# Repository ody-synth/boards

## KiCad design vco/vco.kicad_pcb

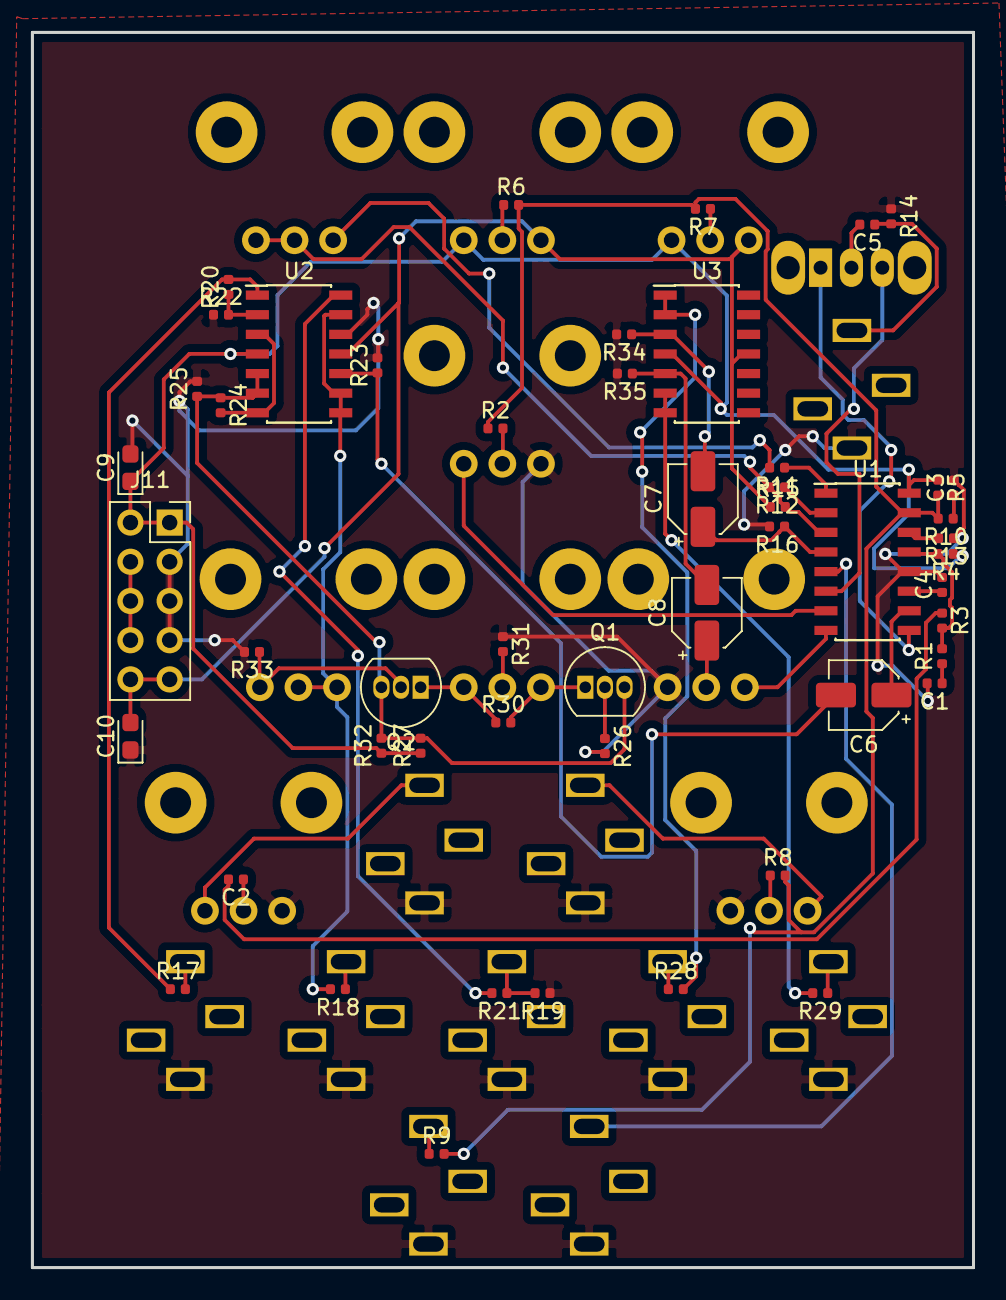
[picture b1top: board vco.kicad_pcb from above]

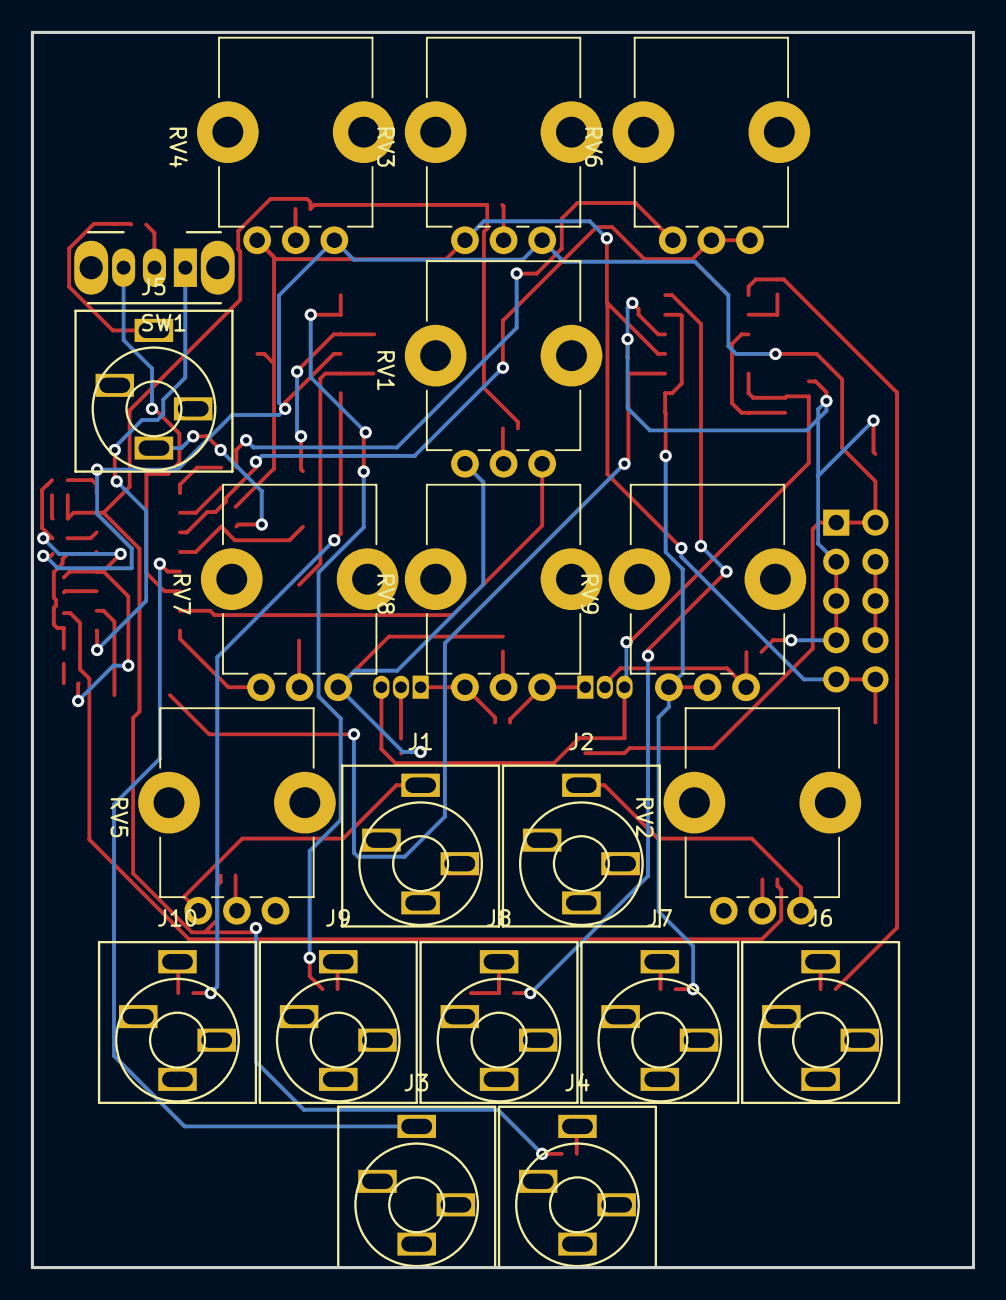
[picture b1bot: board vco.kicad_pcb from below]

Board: 2 copper layers, 61.0 x 80.0 mm, 71 parts (20 on the bottom side), 54 nets.

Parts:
C1, C3: 10nF; C_0402_1005Metric
C2: 100nF; C_0402_1005Metric
C4, C5: 1nF; C_0402_1005Metric
C6, C7, C8: 47uF; CP_Elec_4x5.4
C9, C10: 10uF; CP_EIA-2012-12_Kemet-R
J1: EXP_FM; jack_audio
J2: LIN_FM; jack_audio
J3: PWM_IN; jack_audio
J4: CV 1V/OCT; jack_audio
J5: SYNC_IN; jack_audio
J6: SINE; jack_audio
J7: TRI; jack_audio
J8: SQUARE; jack_audio
J9: PULSE; jack_audio
J10: SAW; jack_audio
J11: Conn_02x05_Odd_Even; PinSocket_2x05_P2.54mm_Vertical
Q1, Q2: 2N3904; TO-92_Inline
R1, R10, R26, R33: 470; R_0402_1005Metric
R2, R3: 1M; R_0402_1005Metric
R4: 1.5M; R_0402_1005Metric
R5: 360K; R_0402_1005Metric
R6: 1.2M; R_0402_1005Metric
R7: 5.6M; R_0402_1005Metric
R8, R9, R14: 100K; R_0402_1005Metric
R11: 24K; R_0402_1005Metric
R12: 5.6K; R_0402_1005Metric
R13: 1.8k; R_0402_1005Metric
R15: 820; R_0402_1005Metric
R16: 51K; R_0402_1005Metric
R17, R18, R28, R29: 1K; R_0402_1005Metric
R19: 82K; R_0402_1005Metric
R20, R22, R23, R27, R32, R34, R35: 10K; R_0402_1005Metric
R21: 15K; R_0402_1005Metric
R24, R25: 22K; R_0402_1005Metric
R30: 220; R_0402_1005Metric
R31: 68K; R_0402_1005Metric
RV1: 20K; Potentiometer_Bourns_PTV09A-1_Single_Vertical
RV2, RV3, RV4, RV5: 100k; Potentiometer_Bourns_PTV09A-1_Single_Vertical
RV6, RV7: 10K; Potentiometer_Bourns_PTV09A-1_Single_Vertical
RV8: 50K; Potentiometer_Bourns_PTV09A-1_Single_Vertical
RV9: 100K; Potentiometer_Bourns_PTV09A-1_Single_Vertical
SW1: SW_SPDT; SW_CuK_OS102011MA1QN1_SPDT_Angled
U1: AS3340; SOIC-16_3.9x9.9mm_P1.27mm
U2, U3: TL074; SOIC-14_3.9x8.7mm_P1.27mm

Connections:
+12V: C9.1, J11.1, J11.2, R4.1, R5.1, R27.1, R32.1, RV3.1, RV4.1, U1.16, U2.4, U3.4
-12V: C10.2, J11.9, J11.10, R15.1, RV3.3, RV4.3, U2.11, U3.11
GND: C1.2, C3.2, C4.2, C9.2, C10.1, J1.S, J2.S, J3.S, J4.S, J5.S, J6.S, J7.S, J8.S, J9.S, J10.S, J11.3, J11.5, J11.7, R13.1, R14.1, R16.2, R19.1, R22.1, R23.2, R25.2, R26.2, R31.1, R33.2, R34.2, R35.2, RV1.3, RV2.3, RV5.1, RV7.1, U1.12, U2.12
unnamed: C1.1, R1.1
unnamed: C2.1, RV2.2
unnamed: C2.2, R3.1
unnamed: C3.1, R10.1
unnamed: C4.1, U1.11
unnamed: C5.1, J5.T, R14.2
unnamed: C5.2, SW1.2
unnamed: C6.2, R23.1, U2.10
unnamed: C7.2, R34.1, U3.3
unnamed: C8.2, R35.1, U3.5
unnamed: J1.T, RV5.3
unnamed: J2.T, RV2.1
unnamed: J4.T, R9.1
unnamed: J6.T, R17.2
unnamed: J7.T, R18.1
unnamed: J8.T, R19.2, R21.1
unnamed: J9.T, R28.1
unnamed: J10.T, R29.1
unnamed: J11.4, J11.6, J11.8
unnamed: Q1.1, R30.2, RV8.3
unnamed: Q1.2, R26.1
unnamed: Q1.3, Q2.3, R24.1, R25.1, R27.2, R32.2, U2.5, U2.6
unnamed: Q2.1, R30.1, RV8.1
unnamed: Q2.2, R33.1, RV9.1
unnamed: R2.2, RV1.2
unnamed: R6.1, RV3.2
unnamed: R7.1, RV4.2
unnamed: R8.1, RV5.2
unnamed: R11.1, U1.1
unnamed: R11.2, RV6.3
unnamed: R12.1, U1.2
unnamed: R13.2, U1.14
unnamed: R17.1, R20.2, U2.1
unnamed: R20.1, R22.2, U2.2
unnamed: R21.2, U2.14
unnamed: R24.2, U2.3, U2.7
unnamed: R28.2, U3.1, U3.2
unnamed: R29.2, U3.6, U3.7
unnamed: R31.2, RV8.2
unnamed: RV7.3, U1.8
PULSE: C7.1, R16.1, U1.4
REE: R12.2, R15.2, RV6.1, RV6.2, U1.3
SAW: C8.1, RV7.2
TRIANGLE: C6.1, U1.10
TRI_OUT: R18.2, RV9.2, RV9.3, U2.8, U2.9, U2.13
VFCI: R2.1, R5.2, R6.2, R7.2, R8.2, R9.2, R10.2, U1.15
VHFT: RV1.1, U1.7
VHSI: SW1.3, U1.6
VLFI: R1.2, R3.2, R4.2, U1.13
VPWM: J3.T, U1.5
VSSI: SW1.1, U1.9

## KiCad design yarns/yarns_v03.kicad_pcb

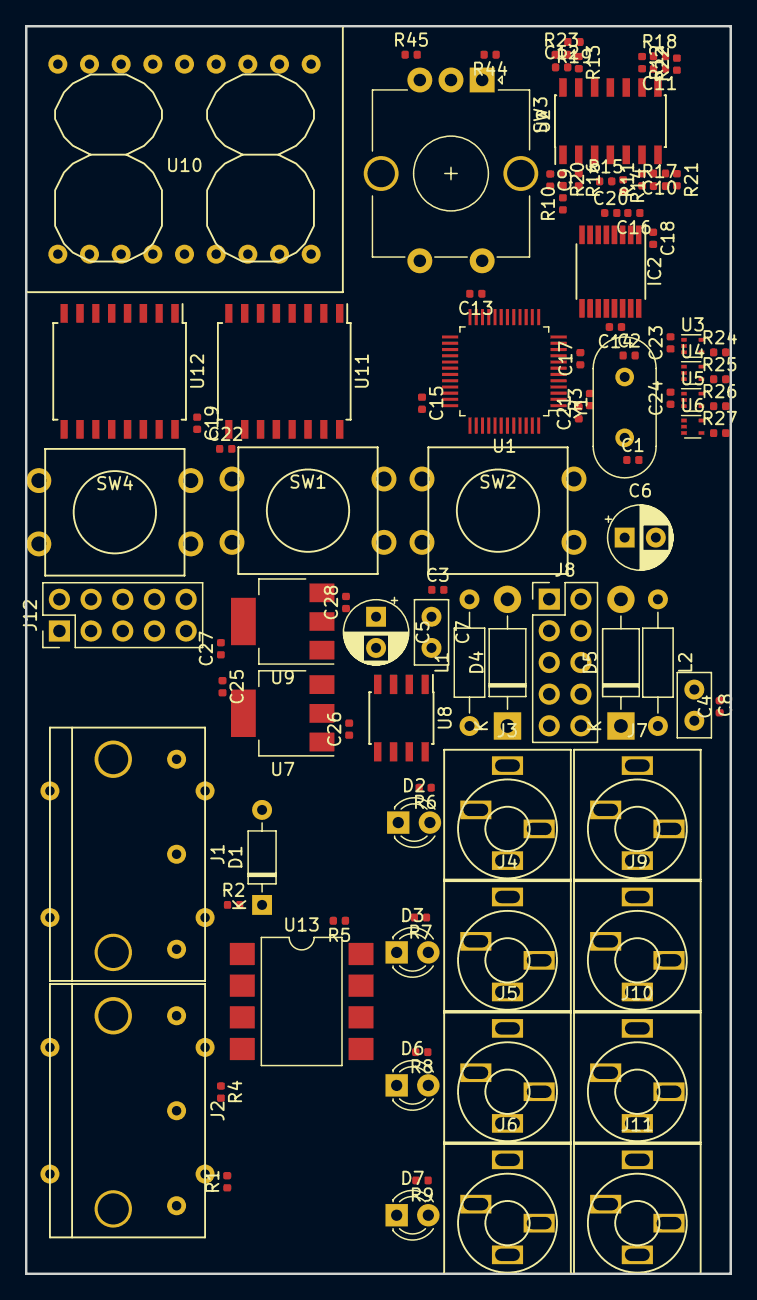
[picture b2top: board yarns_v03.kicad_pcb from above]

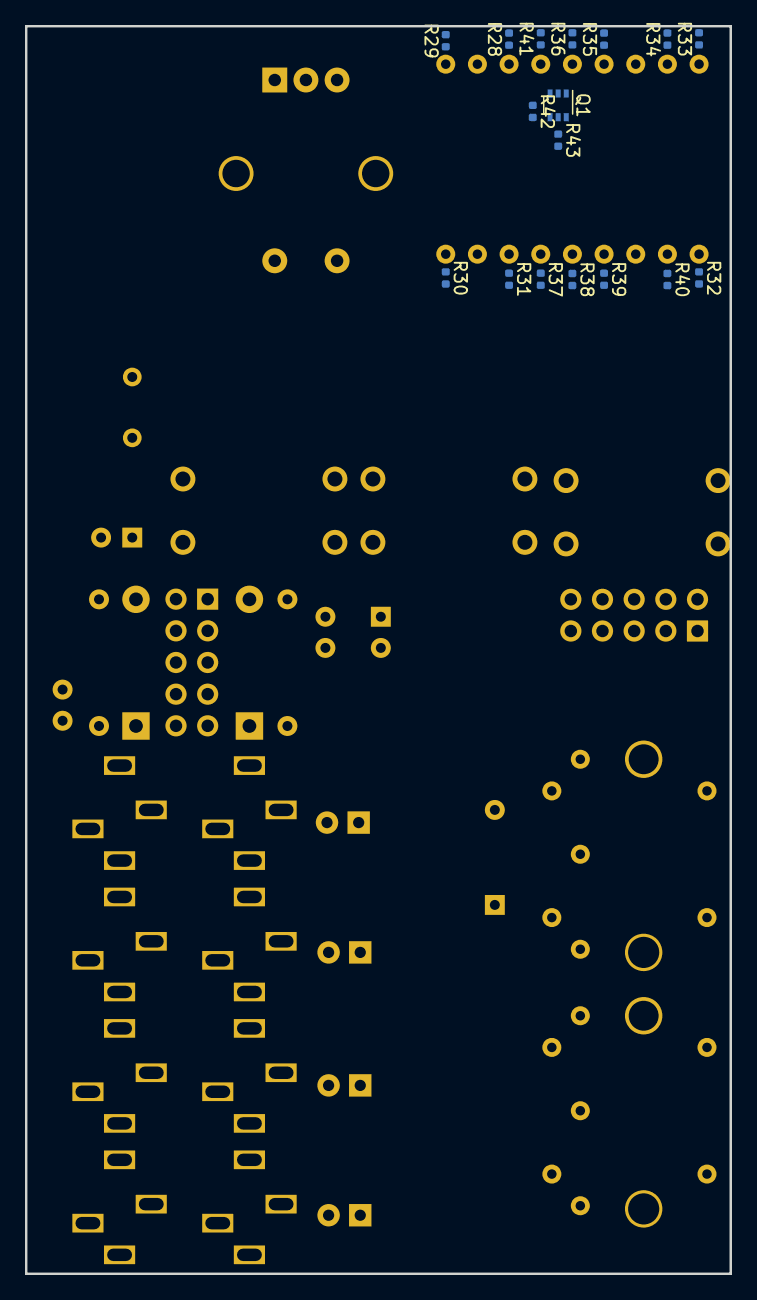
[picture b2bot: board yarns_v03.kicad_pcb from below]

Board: 2 copper layers, 56.5 x 100.1 mm, 114 parts (17 on the bottom side), 112 nets, no tracks yet.

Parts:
C1, C2, C9, C10, C11, C12: 18p; C_0402_1005Metric
C3, C4, C13, C14, C15, C17, C18, C19, C21, C22, C23, C24, C25: 100n; C_0402_1005Metric
C5, C6: 10uF; CP_Radial_D5.0mm_P2.50mm
C7, C8: 100nF; C_Disc_D5.0mm_W2.5mm_P2.50mm
C16: 220n; C_0402_1005Metric
C20: 3.3u; C_0402_1005Metric
C26: 10u; C_0402_1005Metric
C27, C28: 1u; C_0402_1005Metric
D1: 1N4148; D_DO-35_SOD27_P7.62mm_Horizontal
D2, D3, D6, D7: 3MM; LED_D3.0mm
D4, D5: 1N4007; D_DO-41_SOD81_P10.16mm_Horizontal
IC2: DAC8564; TSSOP-16_4.4x5mm_P0.65mm
J1, J2: DIN-5_180degree; MIDI_IN
J3, J4, J5, J6, J7, J9, J10, J11: AudioJack3_Ground; jack_audio
J8, J12: Conn_02x05_Odd_Even; PinHeader_2x05_P2.54mm_Vertical
L1, L2: 22uH; L_Axial_L5.3mm_D2.2mm_P10.16mm_Horizontal_Vishay_IM-1
Q1: MBT3904DW1; SOT-363_SC-70-6
R1, R4: 51; R_0402_1005Metric
R2: 220; R_0402_1005Metric
R3, R5: 10k; R_0402_1005Metric
R6, R7, R8, R9, R28, R29, R30, R31, R32, R33, R34, R35, R36, R37, R38, R39, R40, R41: 100; R_0402_1005Metric
R10, R11, R12, R13, R14, R15: 47k; R_0402_1005Metric
R16, R17, R18, R19: 240k; R_0402_1005Metric
R20, R21, R22, R23, R24, R25, R26, R27, R42, R43, R44, R45: 1k; R_0402_1005Metric
SW1, SW2, SW4: SW_Push_Dual; PUSH_BUTTON
SW3: Rotary_Encoder_Switch; RotaryEncoder_Alps_EC12E-Switch_Vertical_H20mm_CircularMoun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
U1: STM32F103CBTx; LQFP-48_7x7mm_P0.5mm
U2: OPA4134; SOIC-14_3.9x8.7mm_P1.27mm
U3, U4, U5, U6: 74AHCT1G125; SOT-553
U7: LD1117S33TR_SOT223; SOT-223-3_TabPin2
U8: REF02AU; SOIC-8_3.9x4.9mm_P1.27mm
U9: MCP1703A-5002_SOT223; SOT-223-3_TabPin2
U10: KINGBRIGHT-PDC54-11; KINGBRIGHT-PDC54-11GWA
U11, U12: 74HC595; SOIC-16W_7.5x10.3mm_P1.27mm
U13: 6N135S; SMDIP-8_W9.53mm
Y1: 8MHz; Crystal_HC49-U_Vertical

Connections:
12VC: D4.2, J8.1, J8.2
+3V3: C13.2, C14.2, C15.2, C17.2, C19.2, C21.2, C22.2, C26.2, IC2.12, J12.1, R3.1, R4.2, U1.1, U1.9, U1.24, U1.36, U1.48, U7.2, U11.10, U11.16, U12.10, U12.16
+5V: C18.2, C20.2, IC2.4, U8.6
+5VD: C23.2, C24.2, C28.2, U3.5, U4.5, U5.5, U6.5, U9.3
+12V: C3.2, C5.1, C7.1, C25.2, C27.2, L1.2, U2.4, U7.3, U8.2, U9.1
-12VC: D5.1, J8.9, J8.10
/EURORACKPIN/12Vto5V: D4.1, L1.1
CH_A: IC2.1, R10.1
CH_B: IC2.2, R11.1
CH_C: IC2.7, R12.1
CH_D: IC2.8, R13.1
DAC_MOSI: IC2.11, U1.28
DAC_SCK: IC2.10, U1.26
DAC_SS: IC2.9, U1.25
DISP_CHAR0: R42.2, U1.42
DISP_CHAR1: R43.2, U1.41
DISP_EN: U1.45, U11.12, U12.12
DISP_SCK: U1.43, U11.11, U12.11
DISP_SER: U1.46, U11.14
ENC_A: R44.1, U1.2
ENC_B: R45.1, U1.3
ENC_CLICK: SW3.S1, U1.4
GATE_A: U1.21, U3.2
GATE_B: U1.22, U4.2
GATE_C: U1.18, U5.2
GATE_D: U1.19, U6.2
GND: C1.2, C2.2, C3.1, C4.2, C5.2, C6.1, C7.2, C8.1, C13.1, C14.1, C15.1, C16.1, C17.1, C18.1, C19.1, C20.1, C21.1, C22.1, C23.1, C24.1, C25.1, C26.1, C27.1, C28.1, D2.1, D3.1, D6.1, D7.1, IC2.5, IC2.6, IC2.13, IC2.14, IC2.15, IC2.16, J2.3, J3.S, J4.S, J5.S, J6.S, J7.S, J8.3, J8.4, J8.5, J8.6, J8.7, J8.8, J9.S, J10.S, J11.S, J12.3, J12.5, J12.9, Q1.1, Q1.4, R15.1, SW1.1, SW1.3, SW2.1, SW2.3, SW3.C, SW3.S2, SW4.1, SW4.3, U1.8, U1.20, U1.23, U1.35, U1.44, U1.47, U3.1, U3.3, U4.1, U4.3, U5.1, U5.3, U6.1, U6.3, U7.1, U8.4, U9.2, U11.8, U12.8, U13.5
JTCK: J12.4, U1.37
JTDI: J12.8, U1.38
JTDO: J12.6, U1.39
JTMS: J12.2, U1.34
LED1: R6.2, U1.33
LED2: R7.2, U1.32
LED3: R8.2, U1.29
LED4: R9.2, U1.27
MIDI_RX: R5.2, U1.31, U13.6
MIDI_TX: R1.1, U1.30
unnamed: C1.1, U1.5, Y1.1
unnamed: C2.1, U1.6, Y1.2
unnamed: C9.1, R20.1, U2.1
unnamed: C9.2, R10.2, R16.1, U2.2
unnamed: C10.1, R21.1, U2.7
unnamed: C10.2, R11.2, R17.1, U2.6
unnamed: C11.1, R22.1, U2.8
unnamed: C11.2, R12.2, R18.1, U2.9
unnamed: C12.1, R23.1, U2.14
unnamed: C12.2, R13.2, R19.1, U2.13
unnamed: D1.1, R2.2, U13.2
unnamed: D1.2, J1.5, U13.3
unnamed: D2.2, R6.1
unnamed: D3.2, R7.1
unnamed: D5.2, L2.1
unnamed: D6.2, R8.1
unnamed: D7.2, R9.1
unnamed: J1.4, R2.1
unnamed: J2.4, R1.2
unnamed: J2.5, R4.1
unnamed: J3.T, R16.2, R20.2
unnamed: J4.T, R17.2, R21.2
unnamed: J5.T, R18.2, R22.2
unnamed: J6.T, R19.2, R23.2
unnamed: J7.T, R24.2
unnamed: J9.T, R25.2
unnamed: J10.T, R26.2
unnamed: J11.T, R27.2
unnamed: Q1.2, R42.1
unnamed: Q1.3, U10.11
unnamed: Q1.5, R43.1
unnamed: Q1.6, U10.16
unnamed: R5.1, U13.8
unnamed: R24.1, U3.4
unnamed: R25.1, U4.4
unnamed: R26.1, U5.4
unnamed: R27.1, U6.4
unnamed: R28.1, U10.12
unnamed: R28.2, U11.15
unnamed: R29.1, U10.10
unnamed: R29.2, U11.1
unnamed: R30.1, U10.9
unnamed: R30.2, U11.2
unnamed: R31.1, U10.7
unnamed: R31.2, U11.3
unnamed: R32.1, U10.1
unnamed: R32.2, U11.4
unnamed: R33.1, U10.18
unnamed: R33.2, U11.5
unnamed: R34.1, U10.17
unnamed: R34.2, U11.6
unnamed: R35.1, U10.15
unnamed: R35.2, U11.7
unnamed: R36.1, U10.14
unnamed: R36.2, U12.15
unnamed: R37.1, U10.6
unnamed: R37.2, U12.1
unnamed: R38.1, U10.5
unnamed: R38.2, U12.2
unnamed: R39.1, U10.4
unnamed: R39.2, U12.3
unnamed: R40.1, U10.2
unnamed: R40.2, U12.4
unnamed: R41.1, U10.13
unnamed: R41.2, U12.5
unnamed: R44.2, SW3.A
unnamed: R45.2, SW3.B
unnamed: U11.9, U12.14
RESET: J12.10, R3.2, U1.7
SWITCH_0: SW4.2, SW4.4, U1.15
SWITCH_1: SW2.2, SW2.4, U1.16
SWITCH_2: SW1.2, SW1.4, U1.14
VEE: C4.1, C6.2, C8.2, L2.2, U2.11
VREF: C16.2, IC2.3, R14.2
VREF\2: R14.1, R15.2, U2.3, U2.5, U2.10, U2.12

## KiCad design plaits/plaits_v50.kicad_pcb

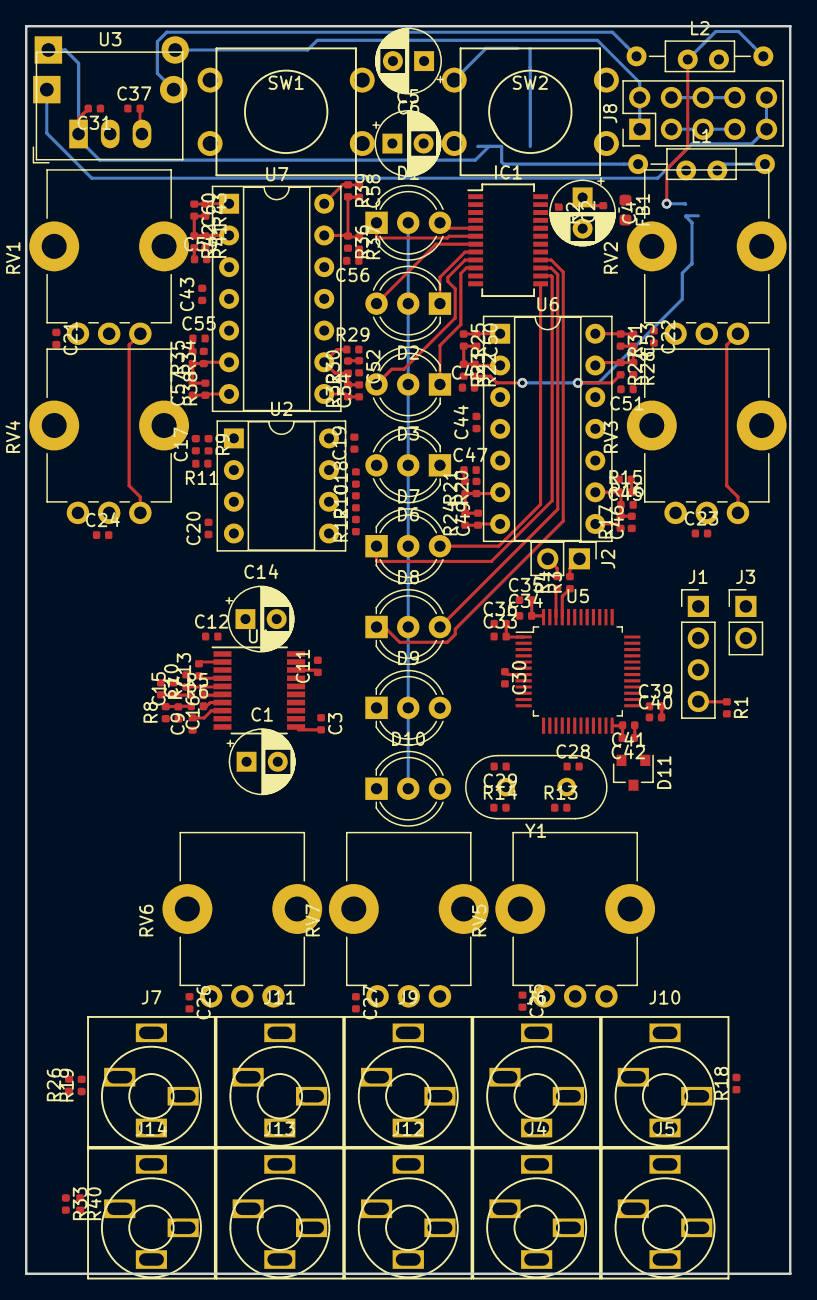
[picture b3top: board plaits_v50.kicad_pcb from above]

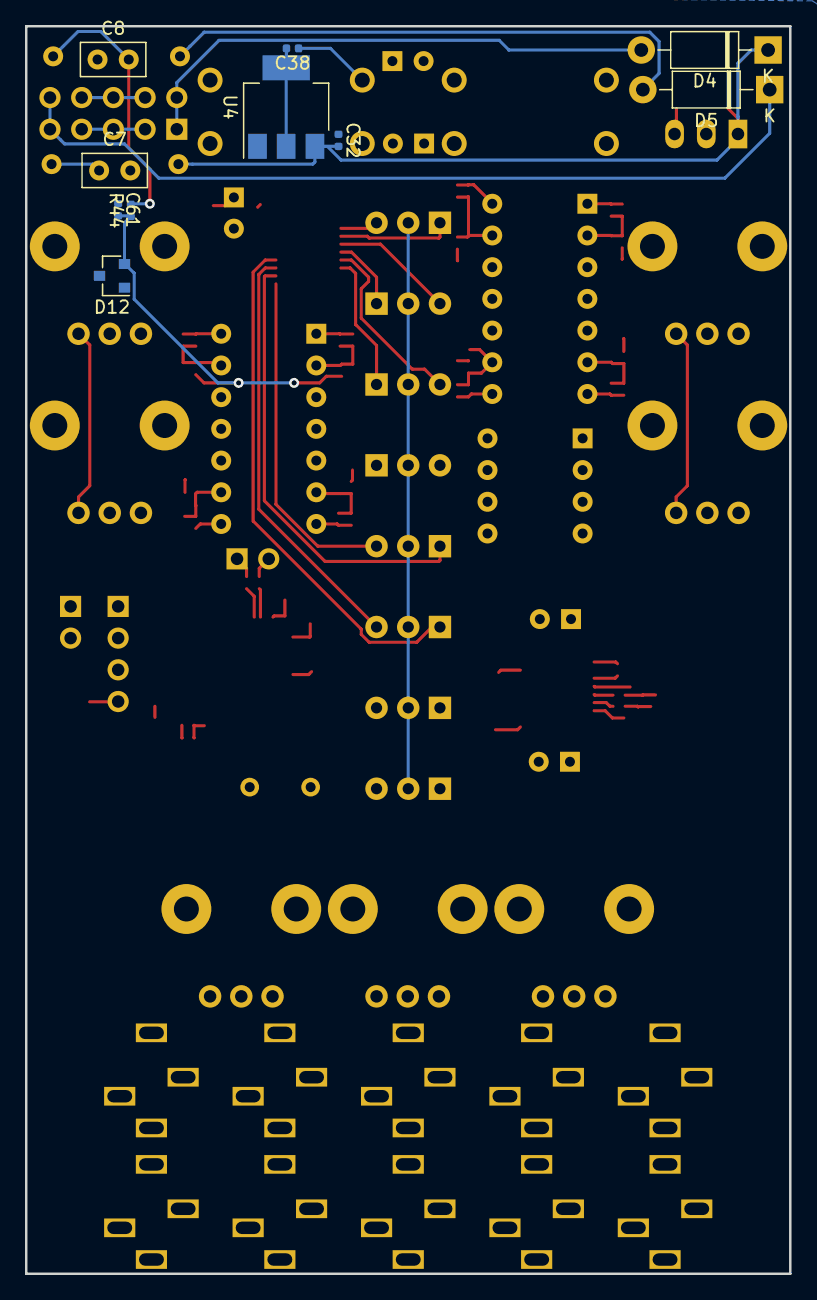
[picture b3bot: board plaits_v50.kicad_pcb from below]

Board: 2 copper layers, 61.2 x 99.9 mm, 152 parts (10 on the bottom side), 99 nets.

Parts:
C1, C4, C5, C6, C14: 10uF; CP_Radial_D5.0mm_P2.50mm
C2, C3, C9, C11, C12, C19, C20, C21, C22, C23, C24, C25, C26, C27, C30, C32, C35, C36, C40, C42, C43, C44: 100nF; C_0402_1005Metric
C7, C8: 100nF; C_Disc_D5.0mm_W2.5mm_P2.50mm
C10, C13: 2.2uF; C_0402_1005Metric
C15, C16, C46, C50, C53, C54, C57, C58: 1nF; C_0402_1005Metric
C17, C18, C49, C60: 100pF; C_0402_1005Metric
C28, C29: 20pF; C_0402_1005Metric
C31, C37, C38: 10uF; C_0402_1005Metric
C33, C34, C39, C41, C61: 1uF; C_0402_1005Metric
C45, C47, C48, C51, C52, C55, C56, C59: ESD; C_0402_1005Metric
D1, D2, D3, D6, D7, D8, D9, D10: SSL-LX3059IGW-CA; LED_D5.0mm-3
D4, D5: 1N4007; D_DO-41_SOD81_P10.16mm_Horizontal
D11: BAT54S; SOT-23
D12: LM4040DBZ-10; SOT-23
FB1: WE-CBF_0603; L_0603_1608Metric
IC1: TLC59281DBQ; SSOP-24_3.9x8.7mm_P0.635mm
J1: Conn_01x04_Male; PinHeader_1x04_P2.54mm_Vertical
J2, J3: Conn_01x02_Male; PinHeader_1x02_P2.54mm_Vertical
J4, J5, J6, J7, J9, J10, J11, J12, J13, J14: AudioJack3_Ground; jack_audio
J8: Conn_02x05_Odd_Even; PinHeader_2x05_P2.54mm_Vertical
L1, L2: 22uH; L_Axial_L5.3mm_D2.2mm_P10.16mm_Horizontal_Vishay_IM-1
R1, R2, R7, R8, R11, R18, R19, R26, R33, R40: 10k; R_0402_1005Metric
R3, R4, R13, R14: 100; R_0402_1005Metric
R5, R6, R44: 2.2k; R_0402_1005Metric
R9, R10, R24, R31, R38, R39: 33k; R_0402_1005Metric
R12: 1k; R_0402_1005Metric
R15, R21, R23, R28, R30, R35, R37, R42: 100k; R_0402_1005Metric
R16, R22, R29: 120k; R_0402_1005Metric
R17, R25, R32: 20k; R_0402_1005Metric
R20, R27, R41: 200k; R_0402_1005Metric
R34: 140k; R_0402_1005Metric
R36: 110k; R_0402_1005Metric
R43: 56k; R_0402_1005Metric
RV1, RV2, RV3, RV4, RV5, RV6, RV7: 10k; Potentiometer_Bourns_PTV09A-1_Single_Vertical
SW1, SW2: SW_Push_Dual; PUSH_BUTTON
U1: PCM5100; TSSOP-20_4.4x6.5mm_P0.65mm
U2: TL072; DIP-8_W7.62mm_Socket
U3: R-783.3-0.5; Converter_DCDC_RECOM_R-78E-0.5_THT
U4: LD1117S33TR_SOT223; SOT-223-3_TabPin2
U5: STM32F373CCTx; LQFP-48_7x7mm_P0.5mm
U6, U7: MCP6004; DIP-14_W7.62mm_Socket
Y1: 8MHz; Crystal_HC49-U_Vertical

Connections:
12VC: D4.2, J8.1, J8.2
12Vto5V: C31.2, C32.2, D4.1, L1.1, U3.1, U4.3
+3.3VA: C9.2, C12.2, C14.1, C38.2, C39.1, C40.1, C41.2, C42.2, C43.1, C44.1, RV1.1, RV2.1, RV3.1, RV4.1, RV5.1, RV6.1, RV7.1, U1.8, U4.2, U5.9, U5.24, U6.4, U7.4
+3V3: C1.1, C3.2, C33.2, C34.2, C35.2, C36.2, C37.2, D1.2, D2.2, D3.2, D6.2, D7.2, D8.2, D9.2, D10.2, D11.2, FB1.2, R1.2, U1.11, U1.17, U1.20, U3.3, U5.1, U5.17, U5.48
+3V3_A: U1.1, U5.25
-12VC: D5.1, J8.9, J8.10
ADC_FM: C50.1, R25.1, U5.22, U6.1
ADC_GATE: C58.1, R39.1, U5.21, U7.14
ADC_HARMONICS: C53.1, R31.1, U5.28, U6.14
ADC_MODEL: C49.1, R24.1, U5.19, U6.7
ADC_MORPH: C46.1, R17.1, U5.27, U6.8
ADC_TIMBRE: C54.1, R32.1, U5.20, U7.8
ADC_TRIG: C60.1, R43.1, U5.18, U7.1
ADC_V_OCT: C57.1, R38.1, U5.26, U7.7
AREF_-10: C61.2, D12.2, R16.2, R20.2, R22.2, R27.2, R29.2, R34.2, R36.2, R41.2, R44.1
DAC_BCK: U1.14, U5.29
DAC_DIN: U1.13, U5.31
DAC_LRCK: U1.15, U5.32
FREQ_ATT: C27.2, RV7.2, U5.15
FREQ_POT: C21.2, RV1.2, U5.10
GND: C1.2, C2.1, C3.1, C4.2, C5.2, C6.1, C7.2, C8.1, C9.1, C10.2, C11.2, C12.1, C14.2, C15.2, C16.2, C19.1, C20.2, C21.1, C22.1, C23.1, C24.1, C25.1, C26.1, C27.1, C28.2, C29.2, C30.2, C31.1, C32.1, C33.1, C34.1, C35.1, C36.1, C37.1, C38.1, C39.2, C40.2, C41.1, C42.1, C43.2, C44.2, C45.2, C47.2, C48.2, C51.2, C52.2, C55.2, C56.2, C59.2, C61.1, D11.1, D12.1, IC1.1, IC1.21, J1.1, J3.1, J3.2, J4.S, J5.S, J6.S, J7.S, J8.3, J8.4, J8.5, J8.6, J8.7, J8.8, J9.S, J10.S, J11.S, J12.S, J13.S, J14.S, R2.2, RV1.3, RV2.3, RV3.3, RV4.3, RV5.3, RV6.3, RV7.3, SW1.1, SW1.3, SW2.1, SW2.3, U1.3, U1.9, U1.10, U1.12, U1.16, U1.19, U2.3, U2.5, U3.2, U4.1, U5.8, U5.23, U5.44, U5.47, U6.3, U6.5, U6.10, U6.11, U6.12, U7.3, U7.5, U7.10, U7.11, U7.12
HARMONICS_POT: C22.2, RV2.2, U5.12
LEDS_SCK: IC1.3, U5.33
LEDS_SIN: IC1.2, U5.35
LEDS_SS: IC1.4, U5.36
MORPH_ATT: C25.2, RV5.2, U5.14
MORPH_POT: C23.2, RV3.2, U5.11
NORMALIZATION_PROBE: D11.3, R18.1, R19.1, R26.1, R33.1, R40.1, U5.30
unnamed: C2.2, C4.1, FB1.1, IC1.24
unnamed: C10.1, U1.5
unnamed: C11.1, U1.18
unnamed: C13.1, U1.4
unnamed: C13.2, U1.2
unnamed: C15.1, R5.1, R7.2
unnamed: C16.1, R6.1, R8.2
unnamed: C17.1, R7.1, R9.2, U2.2
unnamed: C17.2, R9.1, R11.2, U2.1
unnamed: C18.1, R8.1, R10.2, U2.6
unnamed: C18.2, R10.1, R12.2, U2.7
unnamed: C28.1, R13.2, Y1.1
unnamed: C29.1, R14.2, Y1.2
unnamed: C45.1, J6.T, R15.2
unnamed: C46.2, R15.1, R16.1, R17.2, U6.9
unnamed: C47.1, J7.T, R21.2
unnamed: C48.1, J9.T, R23.2
unnamed: C49.2, R20.1, R21.1, R24.2, U6.6
unnamed: C50.2, R22.1, R23.1, R25.2, U6.2
unnamed: C51.1, J10.T, R28.2
unnamed: C52.1, J11.T, R30.2
unnamed: C53.2, R27.1, R28.1, R31.2, U6.13
unnamed: C54.2, R29.1, R30.1, R32.2, U7.9
unnamed: C55.1, J12.T, R35.2
unnamed: C56.1, J13.T, R37.2
unnamed: C57.2, R34.1, R35.1, R38.2, U7.6
unnamed: C58.2, R36.1, R37.1, R39.2, U7.13
unnamed: C59.1, J14.T, R42.2
unnamed: C60.2, R41.1, R42.1, R43.2, U7.2
unnamed: D1.1, IC1.6
unnamed: D1.3, IC1.5
unnamed: D2.1, IC1.8
unnamed: D2.3, IC1.7
unnamed: D3.1, IC1.10
unnamed: D3.3, IC1.9
unnamed: D5.2, L2.1
unnamed: D6.1, IC1.12
unnamed: D6.3, IC1.11
unnamed: D7.1, IC1.14
unnamed: D7.3, IC1.13
unnamed: D8.1, IC1.16
unnamed: D8.3, IC1.15
unnamed: D9.1, IC1.18
unnamed: D9.3, IC1.17
unnamed: D10.1, IC1.20
unnamed: D10.3, IC1.19
unnamed: IC1.23, R2.1
unnamed: J2.1, R3.2
unnamed: J2.2, R4.2
unnamed: J4.T, R11.1
unnamed: J5.T, R12.1
unnamed: J6.G, R18.2
unnamed: J9.G, R19.2
unnamed: J11.G, R26.2
unnamed: J13.G, R33.2
unnamed: J14.G, R40.2
unnamed: R5.2, U1.6
unnamed: R6.2, U1.7
unnamed: R13.1, U5.5
unnamed: R14.1, U5.6
RESET: C30.1, J1.4, R1.1, U5.7
RX: R4.1, U5.46
SWCLK: J1.3, U5.37
SWDIO: J1.2, U5.34
SW_1: SW1.2, SW1.4, U5.43
SW_2: SW2.2, SW2.4, U5.42
TIMBRE_ATT: C26.2, RV6.2, U5.16
TIMBRE_POT: C24.2, RV4.2, U5.13
TX: R3.1, U5.45
VCC: C5.1, C7.1, C19.2, L1.2, U2.8
VEE: C6.2, C8.2, C20.1, L2.2, R44.2, U2.4

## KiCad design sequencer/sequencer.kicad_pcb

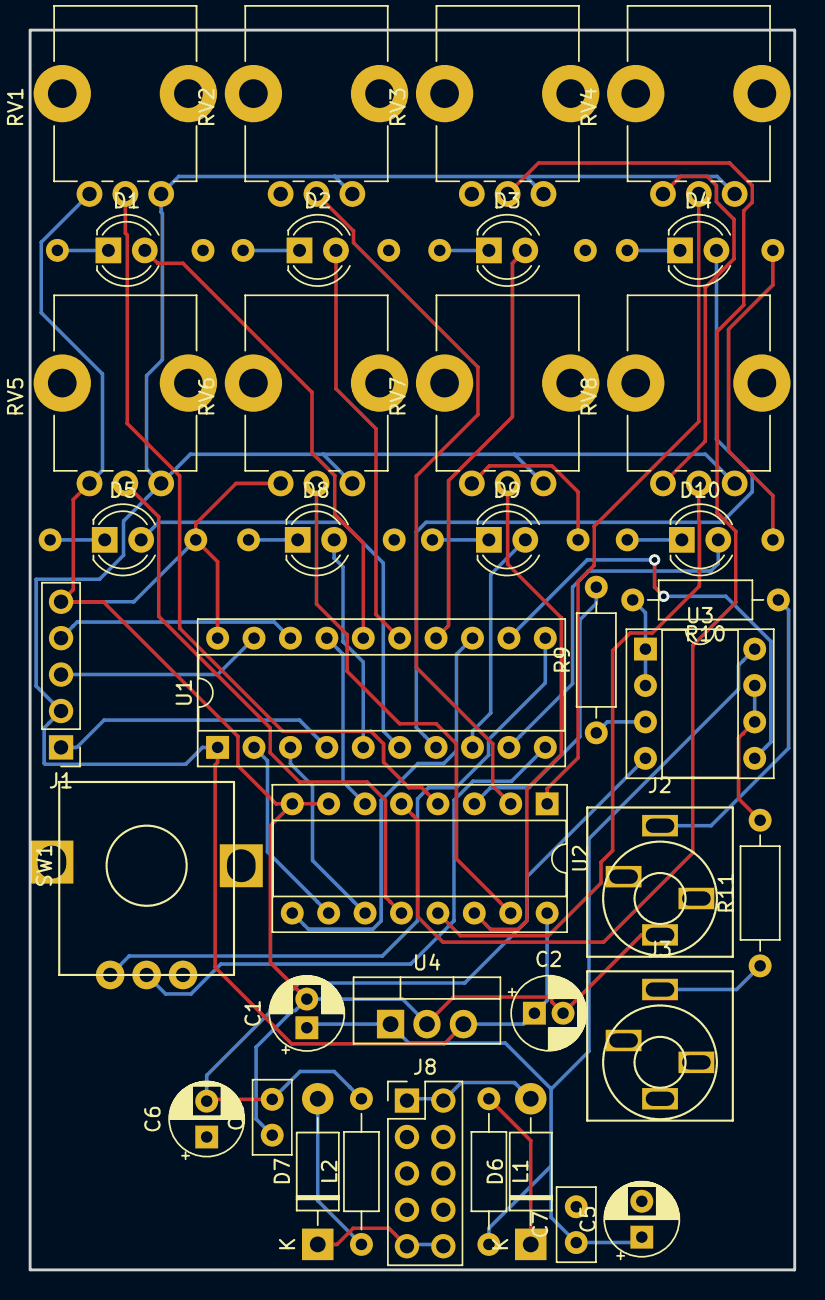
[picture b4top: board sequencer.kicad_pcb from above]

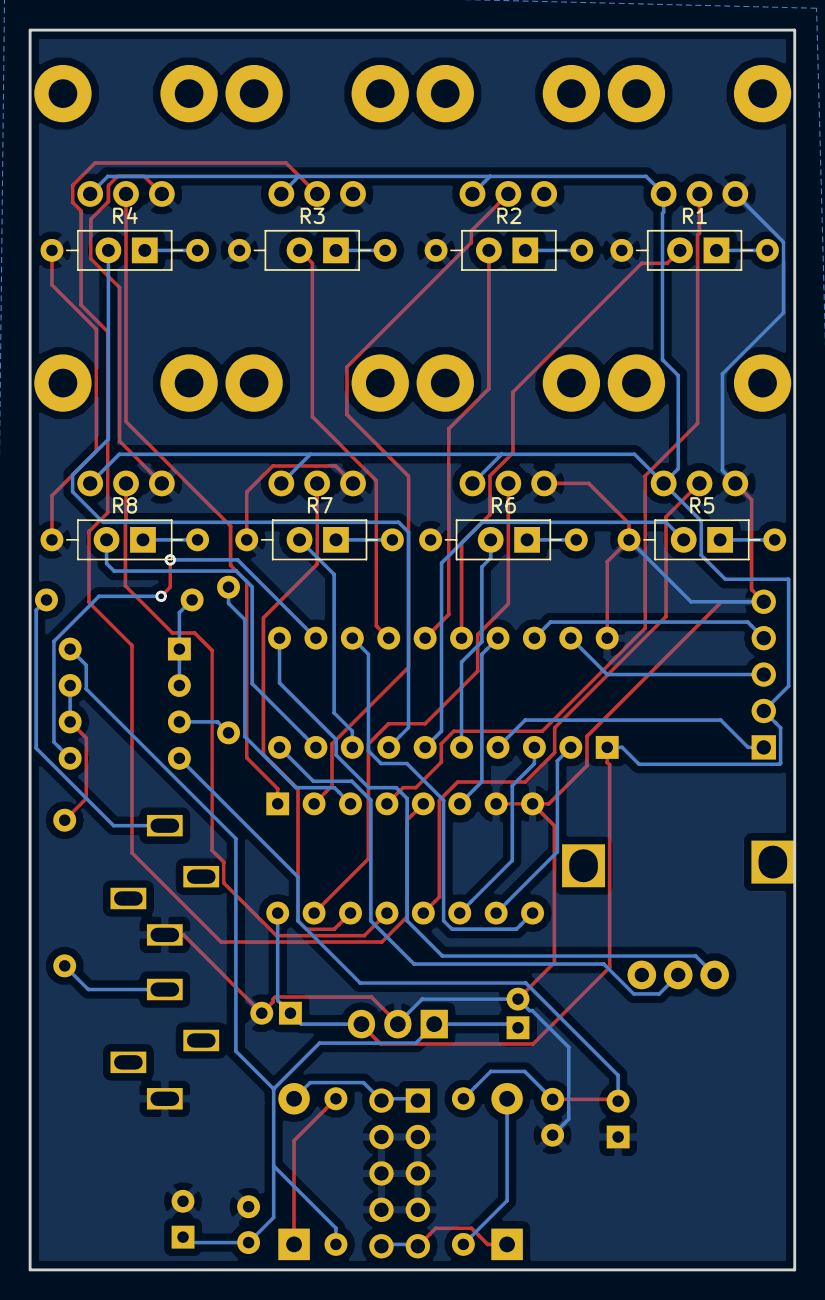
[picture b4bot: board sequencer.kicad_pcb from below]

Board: 2 copper layers, 53.3 x 86.5 mm, 46 parts (8 on the bottom side), 48 nets.

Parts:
C1: 0.33u; CP_Radial_D5.0mm_P2.00mm
C2: 0.1u; CP_Radial_D5.0mm_P2.00mm
C5, C6: 10uF; CP_Radial_D5.0mm_P2.50mm
C7, C8: 100nF; C_Disc_D5.0mm_W2.5mm_P2.50mm
D1, D2, D3, D4, D5, D8, D9, D10: LED; LED_D4.0mm
D6, D7: 1N4007; D_DO-41_SOD81_P10.16mm_Horizontal
J1: Conn_01x05_Male; PinHeader_1x05_P2.54mm_Vertical
J2: CV_OUT; jack_audio
J3: Gate; jack_audio
J8: Conn_02x05_Odd_Even; PinHeader_2x05_P2.54mm_Vertical
L1, L2: 22uH; L_Axial_L5.3mm_D2.2mm_P10.16mm_Horizontal_Vishay_IM-1
R1, R2, R3, R4, R5, R6, R7, R8: 330; R_Axial_DIN0207_L6.3mm_D2.5mm_P10.16mm_Horizontal
R9: 1k; R_Axial_DIN0207_L6.3mm_D2.5mm_P10.16mm_Horizontal
R10, R11: 100; R_Axial_DIN0207_L6.3mm_D2.5mm_P10.16mm_Horizontal
RV1, RV2, RV3, RV4, RV5, RV6, RV7, RV8: 10K; Potentiometer_Bourns_PTV09A-1_Single_Vertical
SW1: Rotary_Encoder; Bourns-PEC12R-N
U1: PIC16F690-IP; DIP-20_W7.62mm_Socket
U2: 4051; DIP-16_W7.62mm_Socket
U3: TL072; DIP-8_W7.62mm_Socket
U4: L7805; TO-220-3_Vertical

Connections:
5V: C2.1, J1.2, RV1.1, RV2.1, RV3.1, RV4.1, RV5.1, RV6.1, RV7.1, RV8.1, U1.1, U2.16, U4.3
12V: C1.1, C5.1, C7.1, L1.2, U3.8, U4.1
12VC: D6.2, J8.1, J8.2
-12VC: D7.1, J8.9, J8.10
/EURORACKPIN/12Vto5V: D6.1, L1.1
/EURORACKPIN/-12V: C6.2, C8.2, L2.2, U3.4
A: U1.3, U2.11
B: U1.2, U2.10
C: U1.13, U2.9
EN: U1.17, U2.6
GND: C1.2, C2.2, C5.2, C6.1, C7.2, C8.1, J1.5, J2.S, J3.S, J8.3, J8.4, J8.5, J8.6, J8.7, J8.8, R1.1, R2.1, R3.1, R4.1, R5.1, R6.1, R7.1, R8.1, RV1.3, RV2.3, RV3.3, RV4.3, RV5.3, RV6.3, RV7.3, RV8.3, U1.20, U2.7, U2.8, U4.2
ICSPCL: J1.4, U1.18
ICSPDAT: J1.3, U1.19
MCLR: J1.1, U1.4
unnamed: D1.1, R1.2
unnamed: D1.2, U1.16
unnamed: D2.1, R2.2
unnamed: D2.2, U1.15
unnamed: D3.1, R3.2
unnamed: D3.2, U1.14
unnamed: D4.1, R4.2
unnamed: D4.2, U1.7
unnamed: D5.1, R5.2
unnamed: D5.2, U1.6
unnamed: D7.2, L2.1
unnamed: D8.1, R6.2
unnamed: D8.2, U1.5
unnamed: D9.1, R7.2
unnamed: D9.2, U1.8
unnamed: D10.1, R8.2
unnamed: D10.2, U1.9
unnamed: J2.T, R10.1
unnamed: J3.T, R11.1
unnamed: R9.1, U3.3
unnamed: R9.2, U2.3
unnamed: R10.2, U3.1, U3.2
unnamed: R11.2, U3.6, U3.7
unnamed: RV1.2, U2.4
unnamed: RV2.2, U2.2
unnamed: RV3.2, U2.5
unnamed: RV4.2, U2.1
unnamed: RV5.2, U2.12
unnamed: RV6.2, U2.15
unnamed: RV7.2, U2.14
unnamed: RV8.2, U2.13
unnamed: SW1.A, U1.11
unnamed: SW1.B, U1.10
unnamed: U1.12, U3.5

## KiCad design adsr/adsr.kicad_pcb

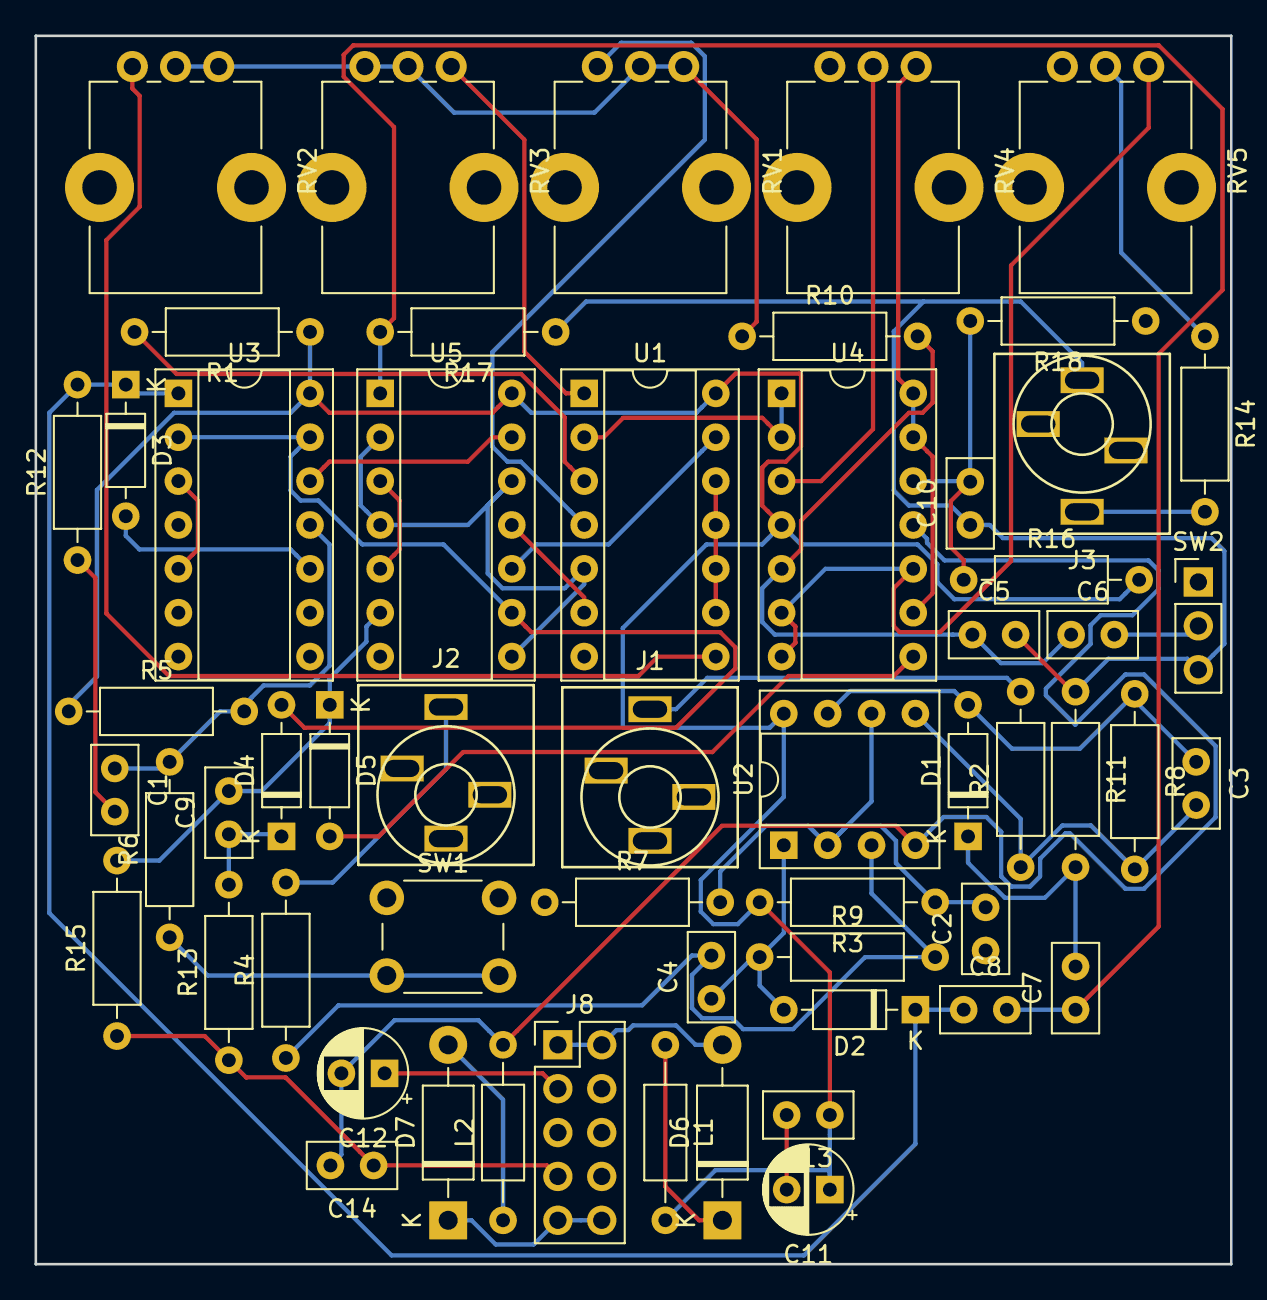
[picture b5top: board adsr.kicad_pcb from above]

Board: 2 copper layers, 69.2 x 71.1 mm, 57 parts (0 on the bottom side), 43 nets.

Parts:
C1, C5: 1uF; C_Disc_D5.0mm_W2.5mm_P2.50mm
C2, C10: 0.1uF; C_Disc_D5.0mm_W2.5mm_P2.50mm
C3, C4: 100pF; C_Disc_D5.0mm_W2.5mm_P2.50mm
C6: 15uF; C_Disc_D5.0mm_W2.5mm_P2.50mm
C7: 0.01uF; C_Disc_D5.0mm_W2.5mm_P2.50mm
C8, C9: 0.001uF; C_Disc_D5.0mm_W2.5mm_P2.50mm
C11, C12: 10uF; CP_Radial_D5.0mm_P2.50mm
C13, C14: 100nF; C_Disc_D5.0mm_W2.5mm_P2.50mm
D1, D2, D3, D4, D5: 1N4148; D_DO-35_SOD27_P7.62mm_Horizontal
D6, D7: 1N4007; D_DO-41_SOD81_P10.16mm_Horizontal
J1: Trigger; jack_audio
J2: Gate; jack_audio
J3: OUT; jack_audio
J8: Conn_02x05_Odd_Even; PinHeader_2x05_P2.54mm_Vertical
L1, L2: 22uH; L_Axial_L5.3mm_D2.2mm_P10.16mm_Horizontal_Vishay_IM-1
R1, R10, R14: 1k; R_Axial_DIN0207_L6.3mm_D2.5mm_P10.16mm_Horizontal
R2, R4, R7: 20k; R_Axial_DIN0207_L6.3mm_D2.5mm_P10.16mm_Horizontal
R3, R15, R17: 100k; R_Axial_DIN0207_L6.3mm_D2.5mm_P10.16mm_Horizontal
R5: 47k; R_Axial_DIN0207_L6.3mm_D2.5mm_P10.16mm_Horizontal
R6, R11, R12, R13, R18: 10k; R_Axial_DIN0207_L6.3mm_D2.5mm_P10.16mm_Horizontal
R8, R9: 1M; R_Axial_DIN0207_L6.3mm_D2.5mm_P10.16mm_Horizontal
R16: 2k; R_Axial_DIN0207_L6.3mm_D2.5mm_P10.16mm_Horizontal
RV1, RV2, RV3: 1M; Potentiometer_Bourns_PTV09A-1_Single_Vertical
RV4: 100k; Potentiometer_Bourns_PTV09A-1_Single_Vertical
RV5: 10k; Potentiometer_Bourns_PTV09A-1_Single_Vertical
SW1: SW_Push; SW_PUSH_6mm_H4.3mm
SW2: SW_SPDT; PinHeader_1x03_P2.54mm_Vertical
U1: 4066; DIP-14_W7.62mm_Socket
U2: TL082; DIP-8_W7.62mm_Socket
U3: 40106; DIP-14_W7.62mm_Socket
U4: TL084; DIP-14_W7.62mm_Socket
U5: 4001; DIP-14_W7.62mm_Socket

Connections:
12V: C11.1, C13.1, L1.2, R1.1, R3.2, R5.1, R16.2, U1.14, U2.8, U3.14, U4.4, U5.14
12VC: D6.2, J8.1, J8.2
-12V: C12.2, C14.2, L2.2, U2.4, U4.11
-12VC: D7.1, J8.9, J8.10
/EURORACKPIN/12Vto5V: D6.1, L1.1
A: U1.5, U5.2, U5.4, U5.8, U5.12
D: U1.13, U5.10
GND: C1.2, C2.1, C5.2, C10.1, C11.2, C12.1, C13.2, C14.1, J1.S, J2.S, J3.S, J8.3, J8.4, J8.5, J8.6, J8.7, J8.8, R7.1, R11.1, R12.1, R13.1, R15.1, R17.1, R18.1, RV4.1, RV5.1, SW1.1, SW2.3, U1.7, U1.9, U1.10, U1.11, U1.12, U3.3, U3.5, U3.7, U3.9, U5.7
Gate: C7.1, C8.2, R17.2, U5.1
Man-Gate: C8.1, D2.1, D3.1, R12.2, U3.1
unnamed: C1.1, R5.2, R6.2, U3.11
unnamed: C2.2, R3.1, R7.2, U2.2, U2.6
unnamed: C3.1, D1.2, R8.1, U2.7
unnamed: C3.2, R2.1, R8.2, U2.5
unnamed: C4.1, D2.2, R9.1, U2.1
unnamed: C4.2, R4.1, R9.2, U2.3
unnamed: C5.1, C6.1, R10.2, U4.5
unnamed: C6.2, SW2.2
unnamed: C7.2, D1.1, R11.2
unnamed: C9.1, D4.1, R13.2
unnamed: C10.2, R16.1, R18.2, U4.12
unnamed: D3.2, U3.10
unnamed: D4.2, U3.2, U3.13, U5.9
unnamed: D5.2, U4.8
unnamed: D7.2, L2.1
unnamed: J1.T, R2.2
unnamed: J2.T, R4.2
unnamed: J3.T, R14.2
unnamed: R1.2, U1.3
unnamed: R6.1, SW1.2
unnamed: R10.1, RV1.2, RV1.3, RV2.2, RV2.3, RV3.1, RV3.2
unnamed: R14.1, RV5.2
unnamed: RV1.1, U1.4
unnamed: RV2.1, U1.8
unnamed: RV3.3, U1.1
unnamed: RV4.2, U4.3
unnamed: RV4.3, U4.9, U4.13, U4.14
unnamed: RV5.3, U4.6, U4.7, U4.10
unnamed: U1.2, U4.1, U4.2
unnamed: U3.12, U5.13
unnamed: U5.3, U5.5
O: C9.2, D5.1, R15.2, U5.6
R: U1.6, U5.11
